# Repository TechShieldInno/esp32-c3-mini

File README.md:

# esp32-c3-mini
ESP32 with MPU9250 9-axis Gyro Accelerator Magnetometer Module

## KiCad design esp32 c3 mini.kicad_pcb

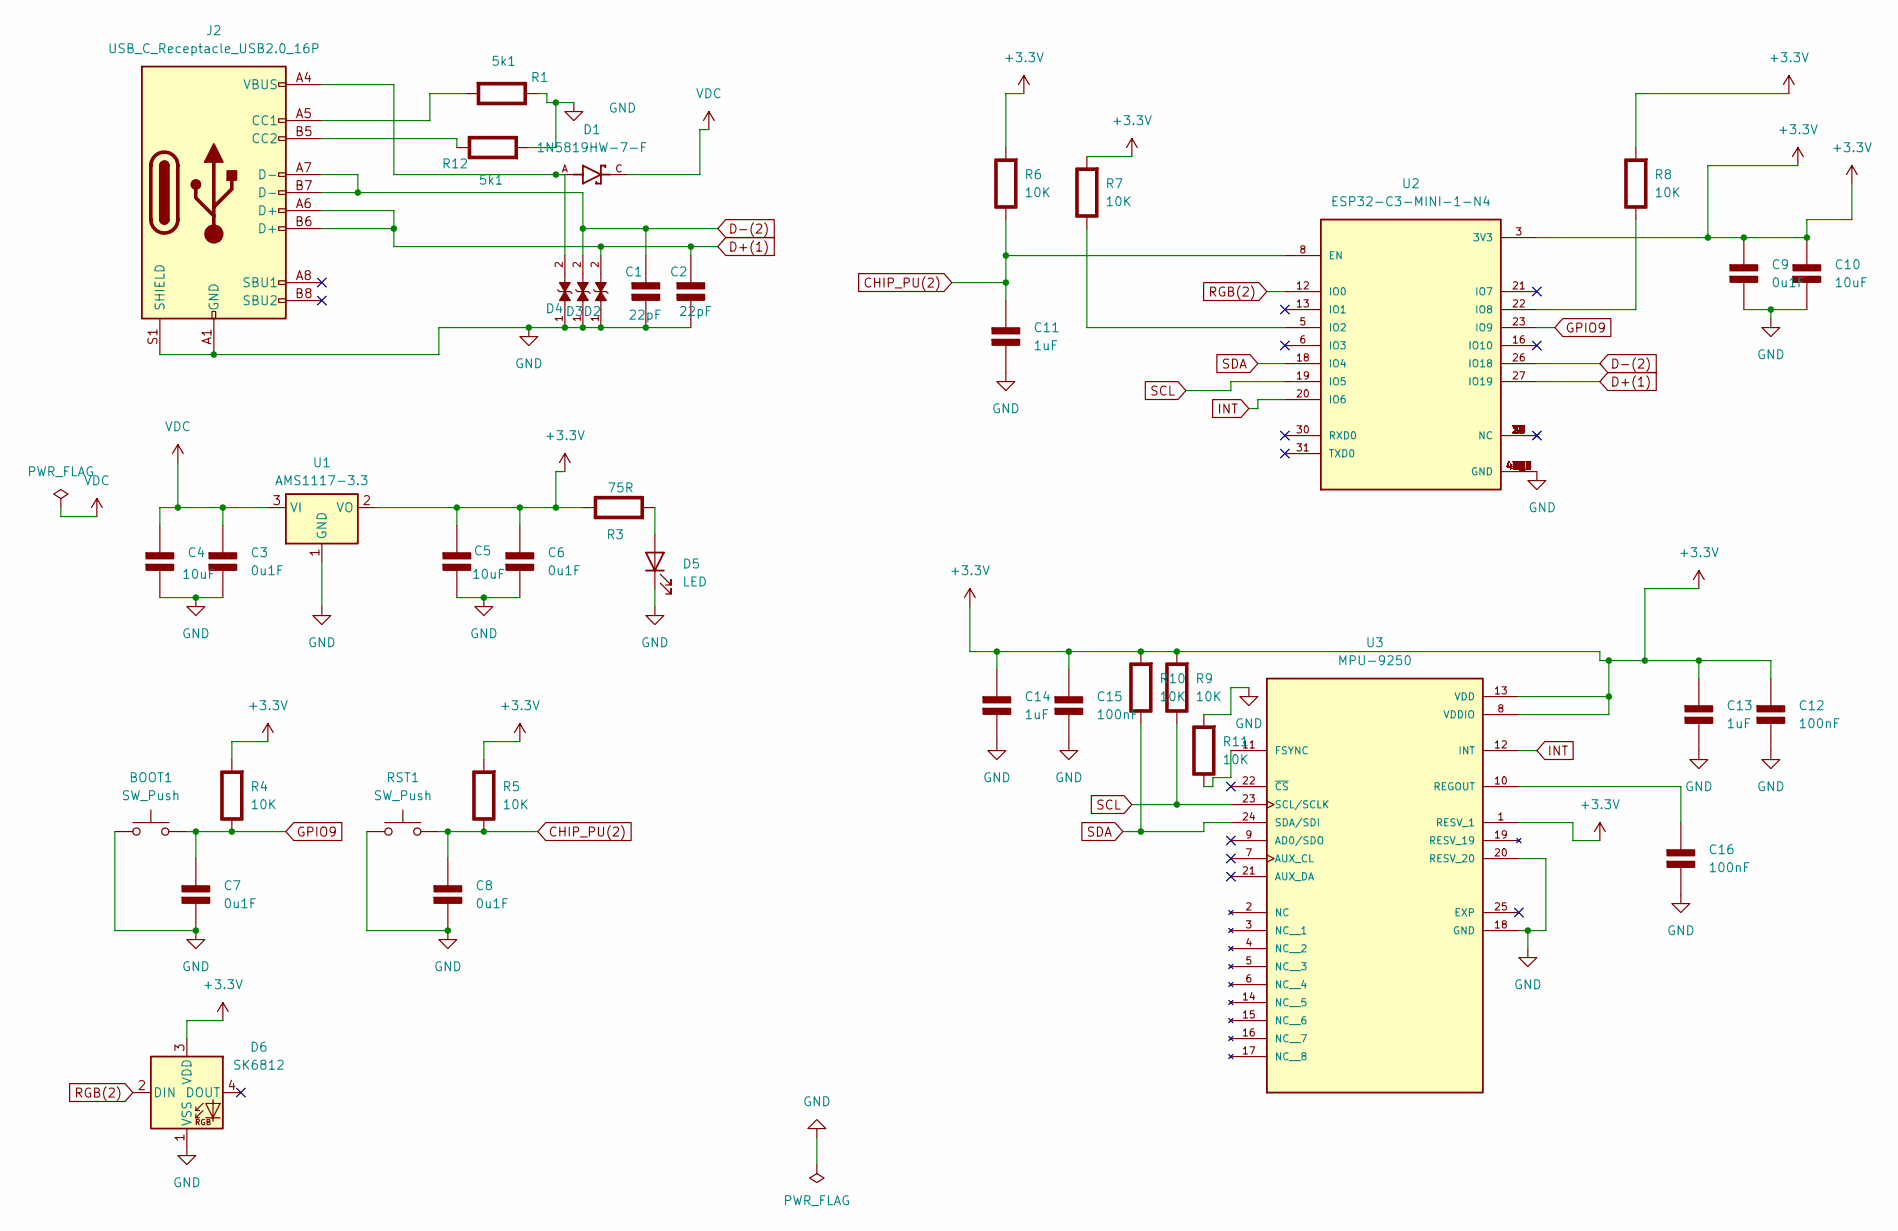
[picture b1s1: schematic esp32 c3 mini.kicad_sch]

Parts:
BOOT1: SW_Push; SW_SPST_B3U-1000P
C1, C2: 22pF; C_0603_1608Metric; Rating V
C3, C6, C7, C8, C9: 0u1F; C_0603_1608Metric; Rating V
C4, C5, C10: 10uF; C_0603_1608Metric; Rating V
C11, C13, C14: 1uF; C_0603_1608Metric; Rating V
C12, C15, C16: 100nF; C_0603_1608Metric; Rating V
D1: 1N5819HW-7-F; SOD3715X145N; PARTREV 18-2
D2, D3, D4: LESD5D5.0CT1G; TVS_LESD5D5.0CT1G; PARTREV O
D5: LED; LED_0603_1608Metric
D6: SK6812; LED_SK6812_PLCC4_5.0x5.0mm_P3.2mm
J2: USB_C_Receptacle_USB2.0_16P; USB_C_Receptacle_GCT_USB4110
R1, R12: 5k1; R_0603_1608Metric; Rating W
R3: 75R; R_0603_1608Metric; Rating W
R4, R5, R6, R7, R8, R9, R10, R11: 10K; R_0603_1608Metric; Rating W
RST1: SW_Push; SW_SPST_B3U-1000P
U1: AMS1117-3.3; SOT-223-3_TabPin2
U2: ESP32-C3-MINI-1-N4; XCVR_ESP32-C3-MINI-1-N4; PARTREV v1.0
U3: MPU-9250; QFN40P300X300X105-25N; PARTREV 1.1

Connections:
+3.3V: C5.1 (+), C6.1 (+), C9.1 (+), C10.1 (+), C12.1 (+), C13.1 (+), C14.1 (+), C15.1 (+), D6.3 (VDD), R3.1 (+), R4.2 (-), R5.2 (-), R6.2 (-), R7.2 (-), R8.2 (-), R9.2 (-), R10.2 (-), U1.2 (VO), U2.3 (3V3), U3.1 (RESV_1), U3.8 (VDDIO), U3.13 (VDD)
CHIP_PU(2): C8.1 (+), C11.1 (+), R5.1 (+), R6.1 (+), RST1.2, U2.8 (EN)
D+(1): C2.1 (+), D2.2, J2.A6 (D+), J2.B6 (D+), U2.27 (IO19)
D-(2): C1.1 (+), D3.2, J2.A7 (D-), J2.B7 (D-), U2.26 (IO18)
GND: BOOT1.1, C1.2 (-), C2.2 (-), C3.2 (-), C4.2 (-), C5.2 (-), C6.2 (-), C7.2 (-), C8.2 (-), C9.2 (-), C10.2 (-), C11.2 (-), C12.2 (-), C13.2 (-), C14.2 (-), C15.2 (-), C16.2 (-), D2.1, D3.1, D4.1, D5.1 (K), D6.1 (VSS), J2.A1 (GND), J2.A12 (GND), J2.B1 (GND), J2.B12 (GND), J2.S1 (SHIELD), R1.1 (+), R11.2 (-), R12.2 (-), RST1.1, U1.1 (GND), U2.1 (GND), U2.2 (GND), U2.11 (GND), U2.14 (GND), U2.36 (GND), U2.37 (GND), U2.38 (GND), U2.39 (GND), U2.40 (GND), U2.41 (GND), U2.42 (GND), U2.43 (GND), U2.44 (GND), U2.45 (GND), U2.46 (GND), U2.47 (GND), U2.48 (GND), U2.49_1 (GND), U2.49_2 (GND), U2.49_3 (GND), U2.49_4 (GND), U2.49_5 (GND), U2.49_6 (GND), U2.49_7 (GND), U2.49_8 (GND), U2.49_9 (GND), U2.50 (GND), U2.51 (GND), U2.52 (GND), U2.53 (GND), U3.18 (GND), U3.20 (RESV_20)
GPIO9: BOOT1.2, C7.1 (+), R4.1 (+), U2.23 (IO9)
INT: U2.20 (IO6), U3.12 (INT)
unnamed: C16.1 (+), U3.10 (REGOUT)
unnamed: D1.A, D4.2, J2.A4 (VBUS), J2.A9 (VBUS), J2.B4 (VBUS), J2.B9 (VBUS)
unnamed: D5.2 (A), R3.2 (-)
unnamed: J2.A5 (CC1), R1.2 (-)
unnamed: J2.B5 (CC2), R12.1 (+)
unnamed: R7.1 (+), U2.5 (IO2)
unnamed: R8.1 (+), U2.22 (IO8)
unnamed: R11.1 (+), U3.11 (FSYNC)
RGB(2): D6.2 (DIN), U2.12 (IO0)
SCL: R9.1 (+), U2.19 (IO5), U3.23 (SCL/SCLK)
SDA: R10.1 (+), U2.18 (IO4), U3.24 (SDA/SDI)
VDC: C3.1 (+), C4.1 (+), D1.C, U1.3 (VI)

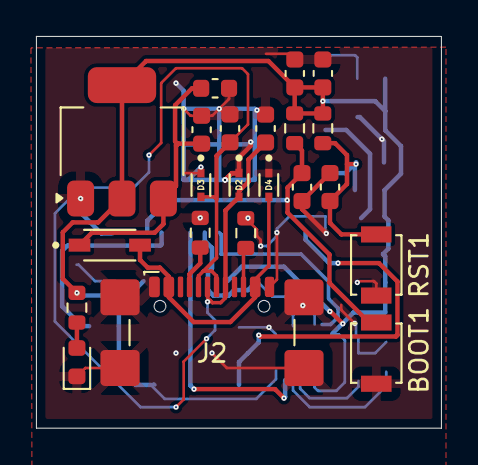
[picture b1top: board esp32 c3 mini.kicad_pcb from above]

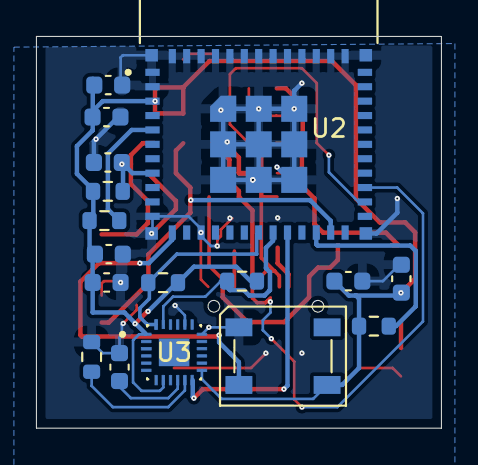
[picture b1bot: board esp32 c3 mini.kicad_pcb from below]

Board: 2 copper layers, 22.5 x 21.8 mm, 39 parts (17 on the bottom side), 19 nets.
